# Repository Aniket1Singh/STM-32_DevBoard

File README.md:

# STM32-Based Development Board  
This repository contains the design files and documentation for a custom STM32-based development board created using KiCad. The board is designed for general-purpose embedded applications and offers robust connectivity and peripheral support.  

---

## Features  
- **Microcontroller**: STM32 (168 MHz Cortex-M4 with FPU).  
- **Memory**:  
  - 1MB Flash.  
  - 192KB SRAM (split into 3 blocks).  
- **Interfaces**:  
  - UART, SPI, I2C.  
  - CAN Bus for communication.  
  - PWM outputs (6 channels).  
- **Power Supply**:  
  - Input Voltage: 5V-12V.  
  - Onboard 3.3V and 5V voltage regulators.  
- **Design Highlights**:  
  - Compact PCB layout.  
  - Overvoltage and reverse polarity protection.  
  - Debugging support via SWD and JTAG.  
  - LED indicators for power, activity, and status.  

---

## Project Files  
This repository includes:  
 **KiCad Project Files**:  
   - Schematic design (.sch).  
   - PCB layout (.kicad_pcb).  
---

## Applications  
- General-purpose embedded systems.  
- Robotics and automation.  
- Communication and control projects.  

---

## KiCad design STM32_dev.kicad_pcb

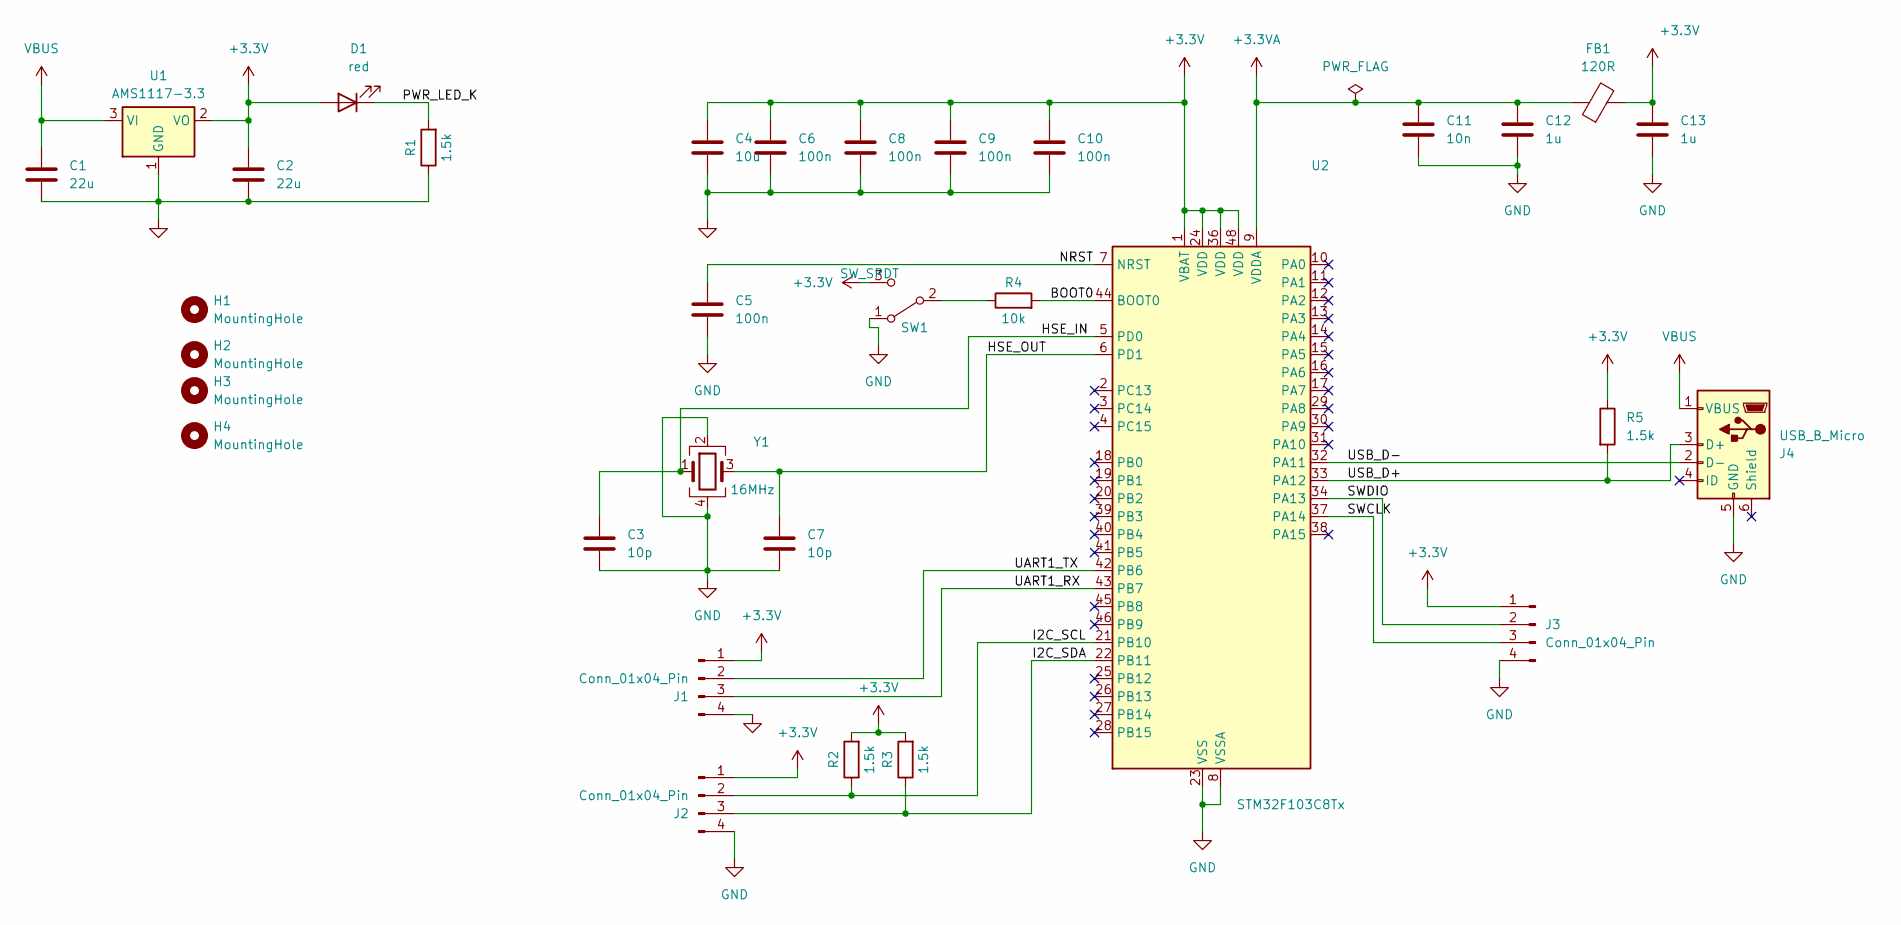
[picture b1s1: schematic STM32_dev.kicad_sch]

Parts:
C1, C2: 22u; C_0805_2012Metric
C3, C7: 10p; C_0402_1005Metric
C4: 10u; C_0201_0603Metric
C5, C6: 100n; C_01005_0402Metric
C8, C9, C10: 100n; C_0402_1005Metric
C11: 10n; C_0402_1005Metric
C12, C13: 1u; C_0402_1005Metric
D1: red; LED_0603_1608Metric
FB1: 120R; L_0603_1608Metric
H1, H2, H3, H4: MountingHole; MountingHole_2.2mm_M2
J1, J2, J3: Conn_01x04_Pin; PinHeader_1x04_P1.27mm_Vertical
J4: USB_B_Micro; USB_Micro-B_Wuerth_629105150521
R1, R2, R3, R5: 1.5k; R_0402_1005Metric
R4: 10k; R_0402_1005Metric
SW1: SW_SPDT; SW_CK_JS202011AQN_DPDT_Angled
U1: AMS1117-3.3; SOT-223-3_TabPin2
U2: STM32F103C8Tx; LQFP-48_7x7mm_P0.5mm
Y1: 16MHz; Crystal_SMD_3225-4Pin_3.2x2.5mm

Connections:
+3.3V: C2.1, C4.1, C6.1, C8.1, C9.1, C10.1, C13.1, D1.2 (A), FB1.2, J1.1, J2.1, J3.1, R2.2, R3.2, R5.1, SW1.3 (C), U1.2 (VO), U2.1 (VBAT), U2.24 (VDD), U2.36 (VDD), U2.48 (VDD); also elsewhere on the board
+3.3VA: C11.1, C12.1, FB1.1, U2.9 (VDDA)
/BOOT0: R4.2, U2.44 (BOOT0)
/HSE_IN: C3.1, U2.5 (PD0), Y1.1
/HSE_OUT: C7.1, U2.6 (PD1), Y1.3
/I2C_SCL: J2.2, R2.1, U2.21 (PB10)
/I2C_SDA: J2.3, R3.1, U2.22 (PB11)
/NRST: C5.1, U2.7 (NRST)
/PWR_LED_K: D1.1 (K), R1.2
/SWCLK: J3.3, U2.37 (PA14)
/SWDIO: J3.2, U2.34 (PA13)
/UART1_RX: J1.3, U2.43 (PB7)
/UART1_TX: J1.2, U2.42 (PB6)
/USB_D+: J4.3 (D+), R5.2, U2.33 (PA12)
/USB_D-: J4.2 (D-), U2.32 (PA11)
GND: C1.2, C2.2, C3.2, C4.2, C5.2, C6.2, C7.2, C8.2, C9.2, C10.2, C11.2, C12.2, C13.2, J1.4, J2.4, J3.4, J4.5 (GND), R1.1, SW1.1 (A), U1.1 (GND), U2.8 (VSSA), U2.23 (VSS), U2.35 (VSS), U2.47 (VSS), Y1.2, Y1.4; also elsewhere on the board
unnamed: R4.1, SW1.2 (B)
VBUS: C1.1, J4.1 (VBUS), U1.3 (VI)

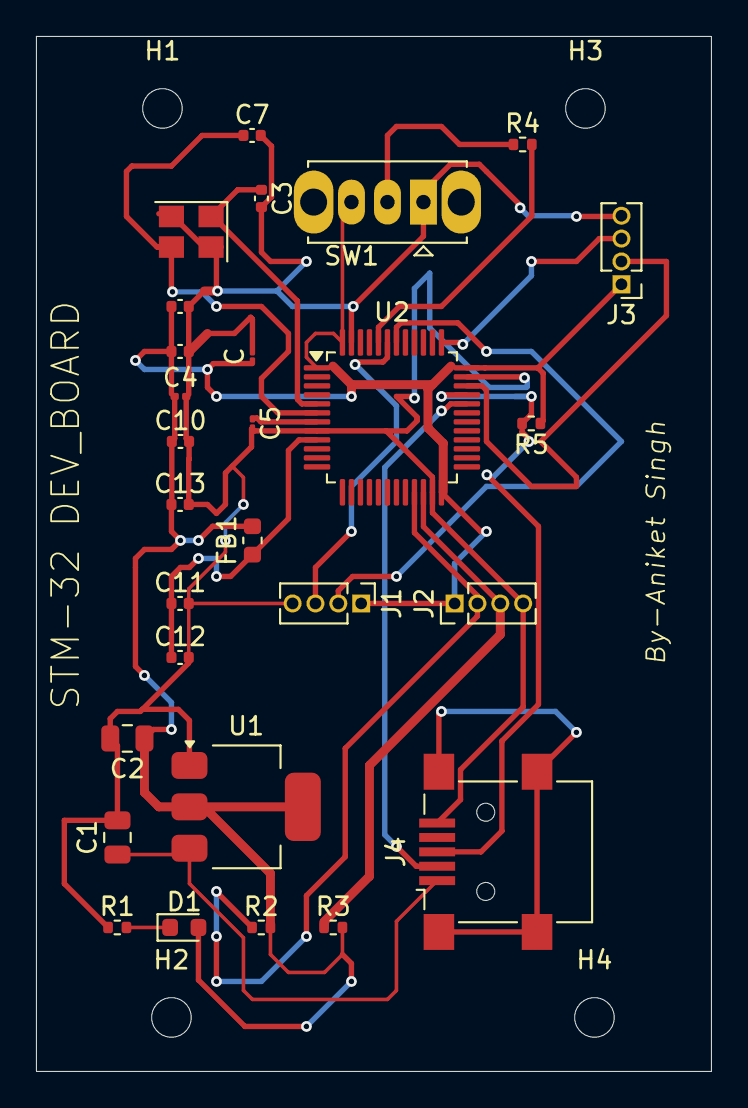
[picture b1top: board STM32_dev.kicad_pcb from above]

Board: 2 copper layers, 37.5 x 57.5 mm, 32 parts (0 on the bottom side), 18 nets.

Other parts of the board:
C: 100n; C_01005_0402Metric

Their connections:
+3.3V: C.1; also elsewhere on the board
GND: C.2; also elsewhere on the board
